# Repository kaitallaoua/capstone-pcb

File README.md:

# Analog Circuit Reliability for Low Earth Orbit Space Applications

In collaboration with the University of Saskatchewan, we are contributing a payload board
for the CubeSats Initiative in Canada for STEM (CUBICS). A CubeSat is a low cost, small
and approachable design for students “to engage in an end-to-end space mission
adapted to their needs and their level of comfort, expertise and readiness” (asc-csa.
gc.ca). Our payload studies the effects of space radiation on commonly used surface
mount analog Integrated Circuits (IC’s) in Low Earth Orbit (LEO). We compare different
shielding to see which provides a better effectiveness to weight ratio.

## Software

Available [here](https://github.com/kaitallaoua/capstone-cubeide)

## Setup

This project used KiCad `Version: 7.0.11-7.0.11~ubuntu22.04.1, release build` and a mix of windows builds.
Download KiCad [here](https://www.kicad.org/download/). KiCad 8 likely does work and I recommend you use it.

## Workflow

TBD (remove this once done): Someone needs to fork this repo to make further contributions to the project. Using an organization is best, I think UofS space team has one, maybe Regina team should make one? Regardless I will not be reviewing and accepting PR's to this repo.

Because using git for KiCad is like tracking binary files, I recommend to NOT rely on git handling merge conflicts. Avoid them entirely by letting only one person make changes on one branch at a time, make a PR, approve and merge and repeat and pass the baton to someone else to make changes.

## TODO

- Get I2C working (unlikely any KiCad changes)
- Get sinewave generation working 
- Add Voltage regulator
- Triple check we fit in PC104, on RADSAT-SK1 printout we dont fit in all holes, also supposed to be some notches?
- Optional: Use solder-attched external non volatile storage such as FLASH, EEPROM (or solder/glue micro sd down??)

The most substantial changes the sinwave generation. This task was assigned to Evan. Ultimately we could not get it working, thus I recommend to use a PWM wave gen from the mcu, likely add pre-amplification + current buffering, and pass it to a sharp drop off filter. The filter could be a dedicated one (probably better) or an op-amp driven one (butterworth?, wont have as good drop off without many stages).

UofRobotics is also making a PCB for their robot whose base is forked from this project, they may be a good reference for questions or idea sharing.

## Manufacturing

We used JLCPCB for `REV A` and `REV B` with great results. We also have nearly all parts ready for another revision. AT LEAST ONE MORE REVISION IS NEEDED SINCE THE FOLLOWING WERE FIXED AFTER `REV B`:

- IC1 footprint solder mask was incorrectly removed
- Micro SD card holder was facing the wrong way

Our manufacturing procedure was as follows:

Order from JLC (1 week delivery), Order from Mouser/Digikey (2-4 day delivery) -> Have all parts -> Go to ED435, use microscope, have one person assist finding parts, one pick+place, apply solder paste (min 4-5 hours)-> place in oven -> done

I recommend to use the parts list available from JLCPCB or PCBWay to assemble as much of the board for you as possible, it saves alot of time but honestly building it by hand it also not that bad. Either is fine.

## Resources

[KiCad 6 STM32 PCB Design Full Tutorial - Phil's Lab #65](https://www.youtube.com/watch?v=aVUqaB0IMh4)

[PCB Design Final Touches (Tips & Checklist) - Phil's Lab #131](https://www.youtube.com/watch?v=g4m91gv-4oQ)

## Front PCB

## Back PCB

## Front Copper Layer

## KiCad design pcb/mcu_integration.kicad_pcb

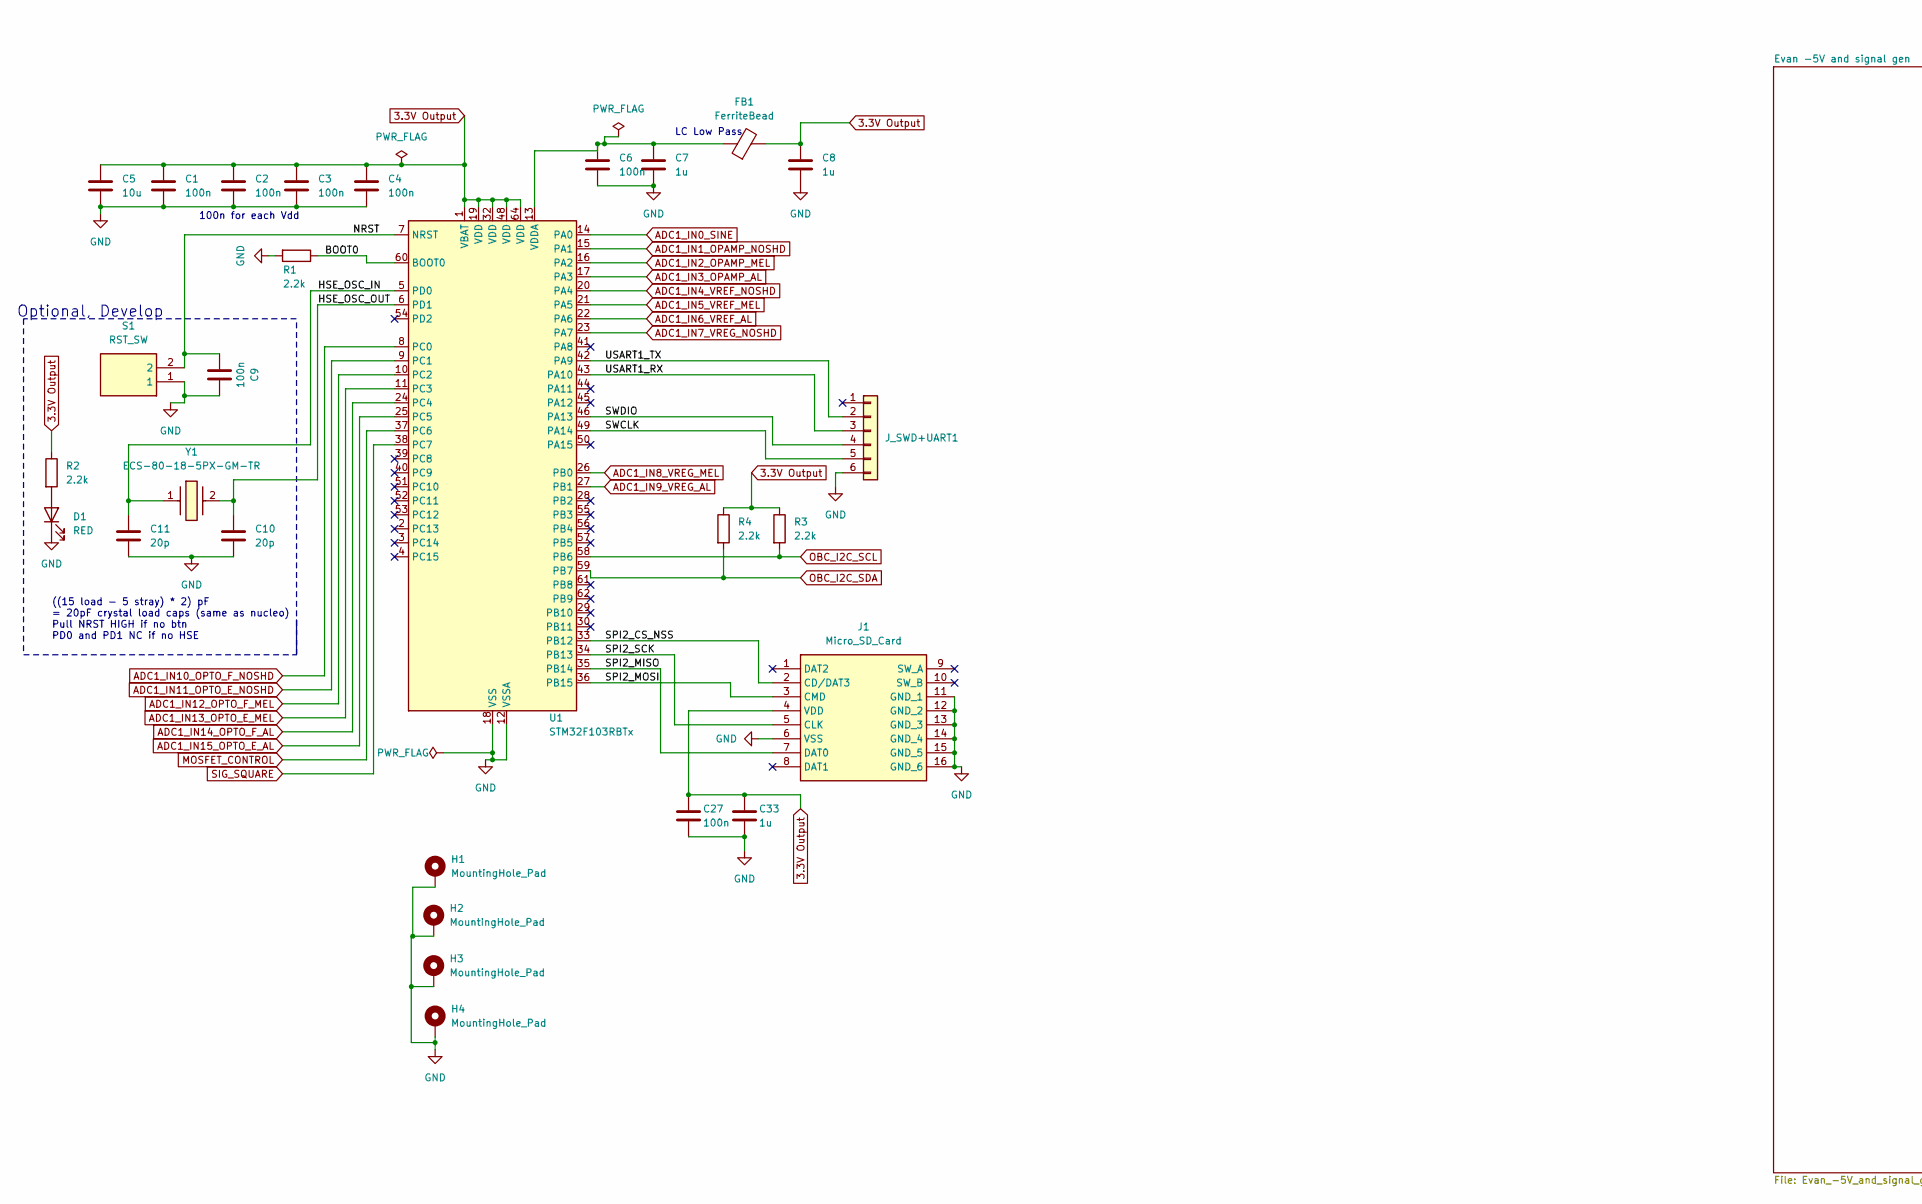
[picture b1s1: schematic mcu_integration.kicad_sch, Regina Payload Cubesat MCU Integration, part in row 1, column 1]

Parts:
C1: 100n; R_0402_1005Metric
C2, C3, C4, C6, C9, C27: 100n; C_0402_1005Metric
C5: 10u; C_0603_1608Metric
C7, C8, C33: 1u; C_0402_1005Metric
C10, C11: 20p; C_0402_1005Metric
D1: RED; LED_0603_1608Metric
FB1: FerriteBead; L_0603_1608Metric
H1, H2, H3, H4: MountingHole_Pad; MountingHole_3.2mm_M3_Pad_Via
J1: Micro_SD_Card; 22017781; Mouser Part Number 571-2201778-1
J_SWD+UART1: Conn_01x06; PinHeader_1x06_P2.54mm_Vertical
R1, R2, R3, R4: 2.2k; R_0402_1005Metric
S1: RST_SW; 95C04A3GWRT; Mouser Part Number 706-95C04A3GWRT
U1: STM32F103RBTx; LQFP-64_10x10mm_P0.5mm
Y1: ECS-80-18-5PX-GM-TR; ECS80185PXGMTR; Mouser Part Number 520-80-18-5PX-GM-TR

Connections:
3.3V Output: C1.1, C2.1, C3.1, C4.1, C5.1, C8.1, C27.1, C33.1, FB1.2, J1.4 (VDD), R2.1, R3.1, R4.1, U1.1 (VBAT), U1.19 (VDD), U1.32 (VDD), U1.48 (VDD), U1.64 (VDD); also elsewhere on the board
/BOOT0: R1.1, U1.60 (BOOT0)
/HSE_OSC_IN: C11.1, U1.5 (PD0), Y1.1
/HSE_OSC_OUT: C10.1, U1.6 (PD1), Y1.2
/NRST: C9.2, S1.2, U1.7 (NRST)
/SPI2_CS_NSS: J1.2 (CD/DAT3), U1.33 (PB12)
/SPI2_MISO: J1.7 (DAT0), U1.35 (PB14)
/SPI2_MOSI: J1.3 (CMD), U1.36 (PB15)
/SPI2_SCK: J1.5 (CLK), U1.34 (PB13)
/SWCLK: J_SWD+UART1.5, U1.49 (PA14)
/SWDIO: J_SWD+UART1.4, U1.46 (PA13)
/USART1_RX: J_SWD+UART1.3, U1.43 (PA10)
/USART1_TX: J_SWD+UART1.2, U1.42 (PA9)
ADC1_IN0_SINE: U1.14 (PA0); also elsewhere on the board
ADC1_IN1_OPAMP_NOSHD: U1.15 (PA1); also elsewhere on the board
ADC1_IN2_OPAMP_MEL: U1.16 (PA2); also elsewhere on the board
ADC1_IN3_OPAMP_AL: U1.17 (PA3); also elsewhere on the board
ADC1_IN4_VREF_NOSHD: U1.20 (PA4); also elsewhere on the board
ADC1_IN5_VREF_MEL: U1.21 (PA5); also elsewhere on the board
ADC1_IN6_VREF_AL: U1.22 (PA6); also elsewhere on the board
ADC1_IN7_VREG_NOSHD: U1.23 (PA7)
ADC1_IN8_VREG_MEL: U1.26 (PB0)
ADC1_IN9_VREG_AL: U1.27 (PB1)
ADC1_IN10_OPTO_F_NOSHD: U1.8 (PC0); also elsewhere on the board
ADC1_IN11_OPTO_E_NOSHD: U1.9 (PC1); also elsewhere on the board
ADC1_IN12_OPTO_F_MEL: U1.10 (PC2); also elsewhere on the board
ADC1_IN13_OPTO_E_MEL: U1.11 (PC3); also elsewhere on the board
ADC1_IN14_OPTO_F_AL: U1.24 (PC4); also elsewhere on the board
ADC1_IN15_OPTO_E_AL: U1.25 (PC5); also elsewhere on the board
GND: C1.2, C2.2, C3.2, C4.2, C5.2, C6.2, C7.2, C8.2, C9.1, C10.2, C11.2, C27.2, C33.2, D1.1 (K), H1.1, H2.1, H3.1, H4.1, J1.6 (VSS), J1.11 (GND_1), J1.12 (GND_2), J1.13 (GND_3), J1.14 (GND_4), J1.15 (GND_5), J1.16 (GND_6), J_SWD+UART1.6, R1.2, S1.1, U1.12 (VSSA), U1.18 (VSS), U1.31 (VSS), U1.47 (VSS), U1.63 (VSS); also elsewhere on the board
MOSFET_CONTROL: U1.37 (PC6); also elsewhere on the board
unnamed: D1.2 (A), R2.2
unnamed: C6.1, C7.1, FB1.1, U1.13 (VDDA)
OBC_I2C_SCL: R3.2, U1.58 (PB6); also elsewhere on the board
OBC_I2C_SDA: R4.2, U1.59 (PB7); also elsewhere on the board
SIG_SQUARE: U1.38 (PC7); also elsewhere on the board

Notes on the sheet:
((15 load - 5 stray) * 2) pF = 20pF crystal load caps (same as nucleo) Pull NRST HIGH if no btn PD0 and PD1 NC if no HSE
Optional, Develop
100n for each Vdd
LC Low Pass

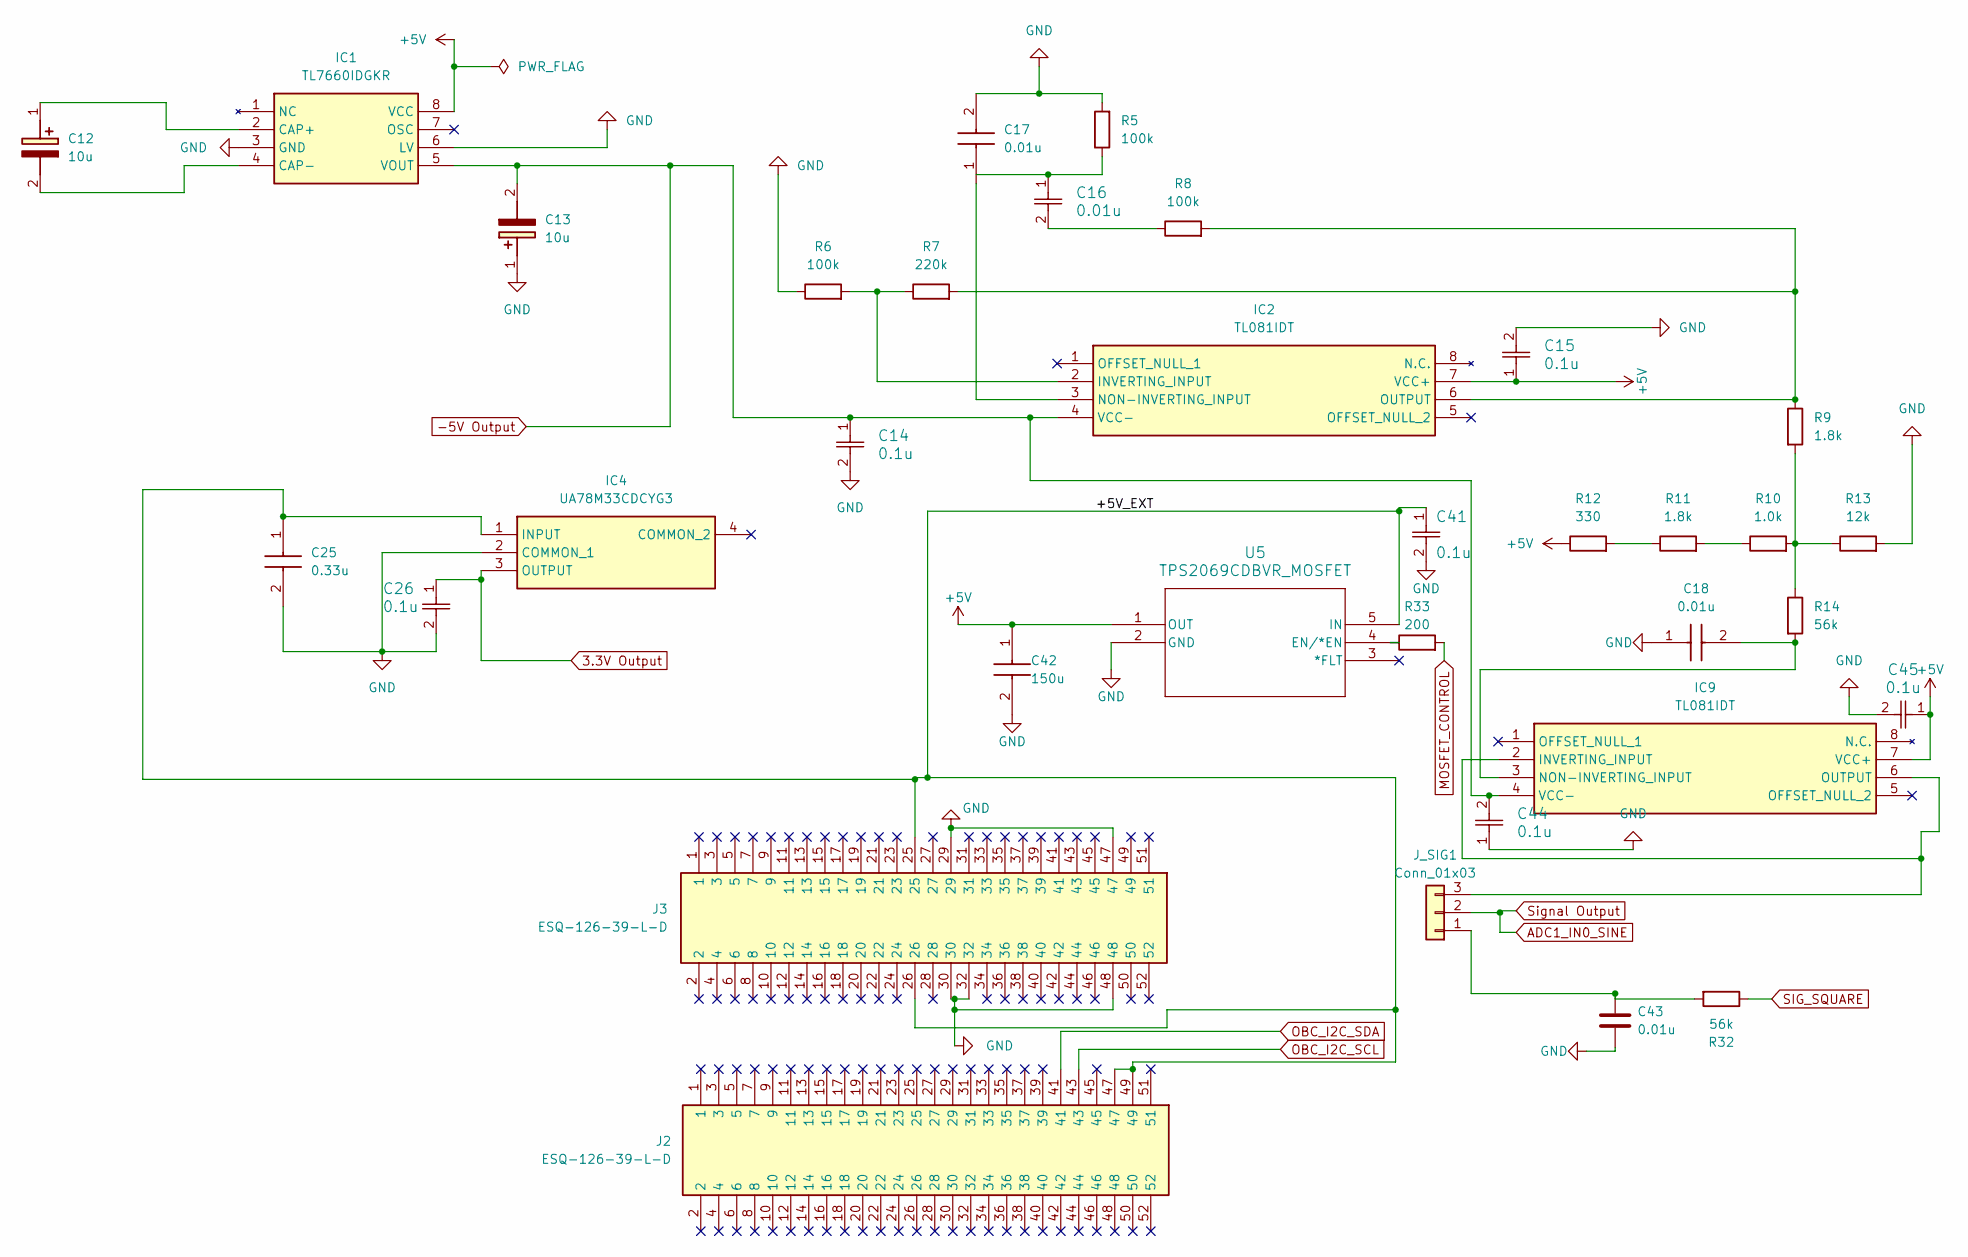
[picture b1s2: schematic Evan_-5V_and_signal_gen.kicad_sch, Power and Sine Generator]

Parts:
C12, C13: 10u; T495D; Mouser Part Number 80-T495D106K035
C14, C15, C26, C41, C44, C45: 0.1u; CAPC220145_88N_KEM-0.1u
C16: 0.01u; CAPC220145_88N_KEM-0.1u
C17, C18: 0.01u; C0805; Mouser Part Number 80-C0805C103F5G
C25: 0.33u; C0805; Mouser Part Number 80-C0805C334K3RAULR
C42: 150u; CAPC3225X280N_150U; Mouser Part Number 187-CL32A157MQVNNNE
C43: 0.01u; C0805
IC1: TL7660IDGKR; SOP65P490X110-8N-actual; Mouser Part Number 595-TL7660IDGKR
IC2, IC9: TL081IDT; SOIC127P600X175-8N; Mouser Part Number 511-TL081IDT
IC4: UA78M33CDCYG3; SOT230P700X180-4N; Mouser Part Number 595-UA78M33CDCYG3
J2, J3: ESQ-126-39-L-D; ESQ-126-Y-X-D; Mouser Part Number 200-ESQ12639LD
J_SIG1: Conn_01x03; PinHeader_1x03_P2.54mm_Vertical
R5, R6, R8: 100k; R_0402_1005Metric
R7: 220k; R_0402_1005Metric
R9, R11: 1.8k; R_0402_1005Metric
R10: 1.0k; R_0402_1005Metric
R12: 330; R_0402_1005Metric
R13: 12k; R_0402_1005Metric
R14, R32: 56k; R_0402_1005Metric
R33: 200; R_0402_1005Metric
U5: TPS2069CDBVR_MOSFET; DBV5_TEX_MF

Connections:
3.3V Output: C26.1, IC4.3 (OUTPUT); also elsewhere on the board
+5V: C15.1, C42.1, C45.1, IC1.8 (VCC), IC2.7 (VCC+), IC9.7 (VCC+), R12.1, U5.1 (OUT); also elsewhere on the board
-5V Output: C13.2 (-), C14.1, C44.2, IC1.5 (VOUT), IC2.4 (VCC-), IC9.4 (VCC-); also elsewhere on the board
/Evan -5V and signal gen/+5V_EXT: C25.1, C41.1, IC4.1 (INPUT), J2.47, J2.49, J3.25, J3.26, U5.5 (IN)
ADC1_IN0_SINE: J_SIG1.2; also elsewhere on the board
GND: C13.1 (+), C14.2, C15.2, C17.2, C18.1, C25.2, C26.2, C41.2, C42.2, C43.1, C44.1, C45.2, IC1.3 (GND), IC1.6 (LV), IC4.2 (COMMON_1), J3.29, J3.30, J3.32, J3.47, J3.48, R5.2, R6.1, R13.2, U5.2 (GND); also elsewhere on the board
MOSFET_CONTROL: R33.2; also elsewhere on the board
unnamed: C12.1 (+), IC1.2 (CAP+)
unnamed: C12.2 (-), IC1.4 (CAP-)
unnamed: C16.1, R5.1
unnamed: C16.2, R8.1
unnamed: IC2.2 (INVERTING_INPUT), R6.2, R7.1
unnamed: C17.1, IC2.3 (NON-INVERTING_INPUT)
unnamed: IC2.6 (OUTPUT), R7.2, R8.2, R9.1
unnamed: IC9.2 (INVERTING_INPUT), IC9.6 (OUTPUT), J_SIG1.3
unnamed: C18.2, IC9.3 (NON-INVERTING_INPUT), R14.2
unnamed: C43.2, J_SIG1.1, R32.2
unnamed: R10.1, R11.2
unnamed: R9.2, R10.2, R13.1, R14.1
unnamed: R11.1, R12.2
unnamed: R33.1, U5.4 (EN/*EN)
OBC_I2C_SCL: J2.43; also elsewhere on the board
OBC_I2C_SDA: J2.41; also elsewhere on the board
SIG_SQUARE: R32.1; also elsewhere on the board

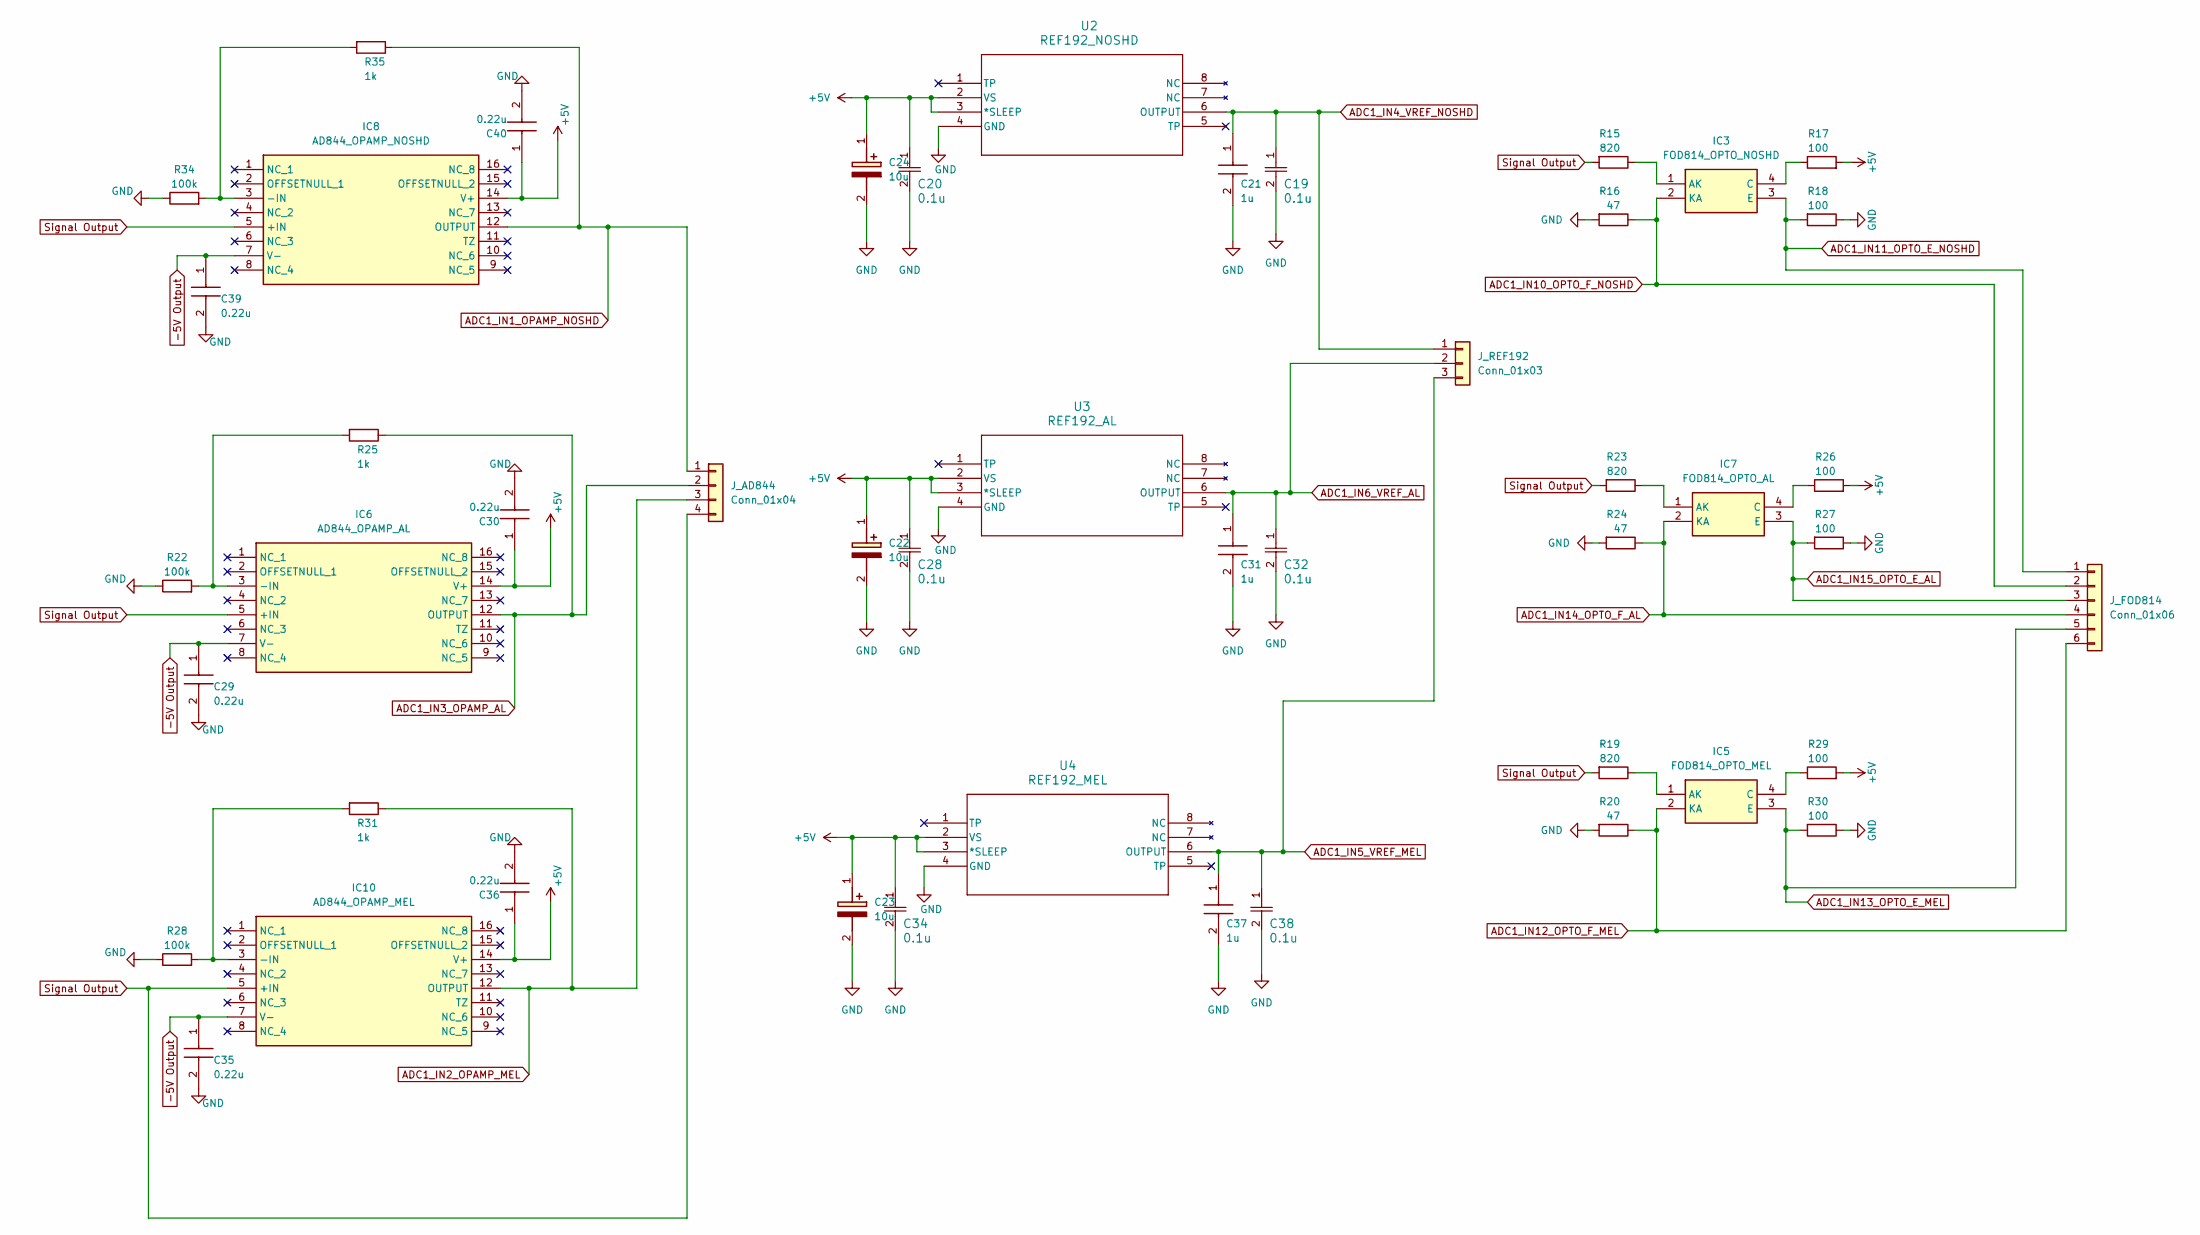
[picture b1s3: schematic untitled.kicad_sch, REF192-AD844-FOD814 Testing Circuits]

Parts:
C19, C20, C28, C32, C34, C38: 0.1u; CAPC220145_88N_KEM-0.1u
C21, C31, C37: 1u; C0805-1u; Mouser Part Number 80-C0805C105Z5VACTU
C22, C23, C24: 10u; T495D; Mouser Part Number 80-T495D106K035
C29, C30, C35, C36, C39, C40: 0.22u; C0805-0.22u; Manufacturer_Part_Number C0805C224M5VACTU
IC3: FOD814_OPTO_NOSHD; SOP254P1016X385-4N-FOD; Mouser Part Number 512-FOD814SD
IC5: FOD814_OPTO_MEL; SOP254P1016X385-4N-FOD; Mouser Part Number 512-FOD814SD
IC6: AD844_OPAMP_AL; SOIC127P1032X265-16N-AD844; Mouser Part Number 584-AD844JRZ-16-R7
IC7: FOD814_OPTO_AL; SOP254P1016X385-4N-FOD; Mouser Part Number 512-FOD814SD
IC8: AD844_OPAMP_NOSHD; SOIC127P1032X265-16N-AD844; Mouser Part Number 584-AD844JRZ-16-R7
IC10: AD844_OPAMP_MEL; SOIC127P1032X265-16N-AD844; Mouser Part Number 584-AD844JRZ-16-R7
J_AD844: Conn_01x04; PinHeader_1x04_P2.54mm_Vertical
J_FOD814: Conn_01x06; PinHeader_1x06_P2.54mm_Vertical
J_REF192: Conn_01x03; PinHeader_1x03_P2.54mm_Vertical
R15, R19, R23: 820; R_0402_1005Metric
R16, R20, R24: 47; R_0402_1005Metric
R17, R18, R26, R27, R29, R30: 100; R_0402_1005Metric
R22, R28, R34: 100k; R_0402_1005Metric
R25, R31, R35: 1k; R_0402_1005Metric
U2: REF192_NOSHD; R_8_ADI-REF
U3: REF192_AL; R_8_ADI-REF
U4: REF192_MEL; R_8_ADI-REF

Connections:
+5V: C20.1, C22.1 (+), C23.1 (+), C24.1 (+), C28.1, C30.1, C34.1, C36.1, C40.1, IC6.14 (V+), IC8.14 (V+), IC10.14 (V+), R17.2, R26.2, R29.2, U2.2 (VS), U2.3 (*SLEEP), U3.2 (VS), U3.3 (*SLEEP), U4.2 (VS), U4.3 (*SLEEP); also elsewhere on the board
-5V Output: C29.1, C35.1, C39.1, IC6.7 (V-), IC8.7 (V-), IC10.7 (V-); also elsewhere on the board
ADC1_IN0_SINE: IC6.5 (+IN), IC8.5 (+IN), IC10.5 (+IN), J_AD844.4, R15.2, R19.2, R23.2; also elsewhere on the board
ADC1_IN1_OPAMP_NOSHD: IC8.12 (OUTPUT), J_AD844.1, R35.1; also elsewhere on the board
ADC1_IN2_OPAMP_MEL: IC10.12 (OUTPUT), J_AD844.3, R31.1; also elsewhere on the board
ADC1_IN3_OPAMP_AL: IC6.12 (OUTPUT), J_AD844.2, R25.1; also elsewhere on the board
ADC1_IN4_VREF_NOSHD: C19.1, C21.1, J_REF192.1, U2.6 (OUTPUT); also elsewhere on the board
ADC1_IN5_VREF_MEL: C37.1, C38.1, J_REF192.3, U4.6 (OUTPUT); also elsewhere on the board
ADC1_IN6_VREF_AL: C31.1, C32.1, J_REF192.2, U3.6 (OUTPUT); also elsewhere on the board
ADC1_IN10_OPTO_F_NOSHD: IC3.2 (KA), J_FOD814.2, R16.1; also elsewhere on the board
ADC1_IN11_OPTO_E_NOSHD: IC3.3 (E), J_FOD814.1, R18.2; also elsewhere on the board
ADC1_IN12_OPTO_F_MEL: IC5.2 (KA), J_FOD814.6, R20.1; also elsewhere on the board
ADC1_IN13_OPTO_E_MEL: IC5.3 (E), J_FOD814.5, R30.2; also elsewhere on the board
ADC1_IN14_OPTO_F_AL: IC7.2 (KA), J_FOD814.4, R24.1; also elsewhere on the board
ADC1_IN15_OPTO_E_AL: IC7.3 (E), J_FOD814.3, R27.2; also elsewhere on the board
GND: C19.2, C20.2, C21.2, C22.2 (-), C23.2 (-), C24.2 (-), C28.2, C29.2, C30.2, C31.2, C32.2, C34.2, C35.2, C36.2, C37.2, C38.2, C39.2, C40.2, R16.2, R18.1, R20.2, R22.1, R24.2, R27.1, R28.1, R30.1, R34.1, U2.4 (GND), U3.4 (GND), U4.4 (GND); also elsewhere on the board
unnamed: IC3.1 (AK), R15.1
unnamed: IC3.4 (C), R17.1
unnamed: IC5.1 (AK), R19.1
unnamed: IC5.4 (C), R29.1
unnamed: IC6.3 (-IN), R22.2, R25.2
unnamed: IC7.1 (AK), R23.1
unnamed: IC7.4 (C), R26.1
unnamed: IC8.3 (-IN), R34.2, R35.2
unnamed: IC10.3 (-IN), R28.2, R31.2

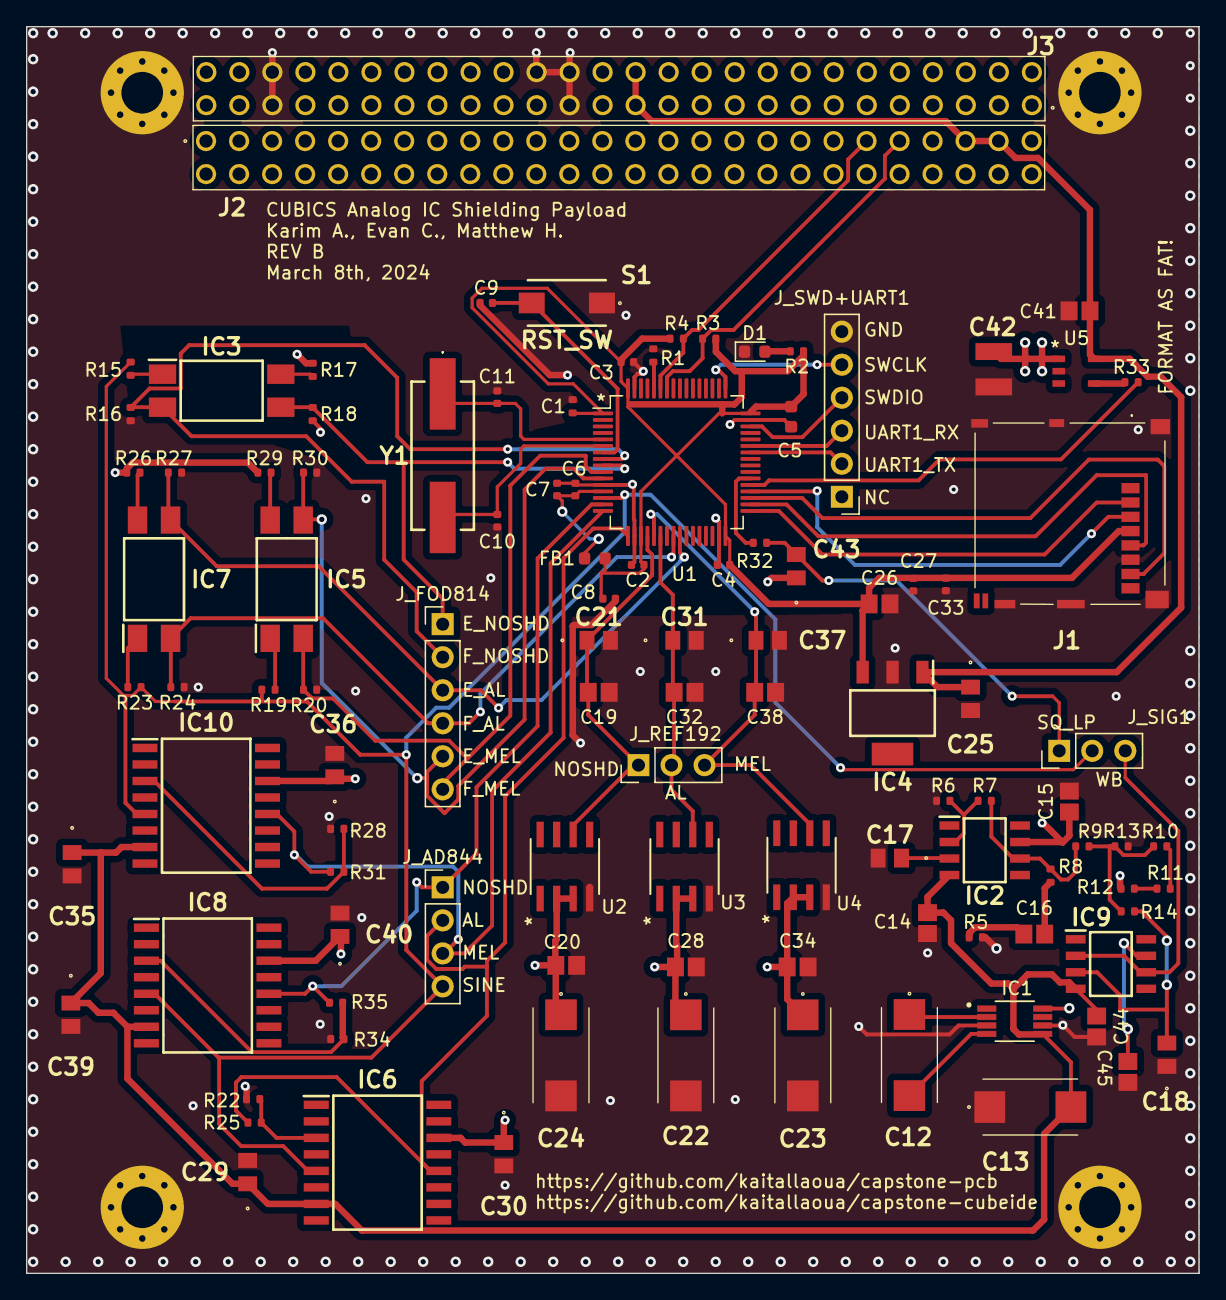
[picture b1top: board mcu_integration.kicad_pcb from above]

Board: 4 copper layers, 90.2 x 95.9 mm, 110 parts (0 on the bottom side), 59 nets.

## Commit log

2024-01-31 mcu_integration sch done
2024-02-06 mcu integration done, 10x10cm pcb+micro sd+osc
2024-02-06 Testing to see what works
2024-02-06 use generic dir
2024-02-06 use generic dir (#2)
2024-02-09 Signal gen and - 5 V circuits added
    I added the two circuits for signal gen and - 5 V all capacitators are speced and in the #links in discord.
2024-02-09 Signal gen and - 5 V circuits added (#3)
    I added the two circuits for signal gen and - 5 V all capacitators are speced and in the #links in discord.
2024-02-09 Changing of resistance values to make the signal voltage 3.0 V
    Changed resistors to make a better signal voltage
2024-02-13 Implemented IC Test portion (AD844, FOD814, REF192)
2024-02-13 Implemented IC Test portion (AD844, FOD814, REF192) (#5)
2024-02-14 Updated resistor values
    updated two resistor values to coincide with changes made to my circuit. R12 and R21 are the names.
2024-02-14 Added labels for ADC's, change R's and C's values to have more of same parts
2024-02-14 Added labels for ADC's, change R's and C's values to have more of same parts (#7)
2024-02-14 Evan---Adding_PC104_Connector
    Added the PC104 connector, added global -5v and signal output labels, changed r12 to 330, and added r21 of 150k.
2024-02-14 Evan---Adding_PC104_Connector (#8)
    Added the PC104 connector, added global -5v and signal output labels, changed r12 to 330, and added r21 of 150k.
2024-02-15 Adding 3.3v reg
    added 3.3v regulator circuit.
2024-02-15 Adding 3.3v reg (#9)
    added 3.3v regulator circuit.
2024-02-16 first bulk commit of routing
2024-02-18 removed about 300 warnings
2024-02-18 removed all pcb DRC errors/warnings
2024-02-18 silkscreen: remove part num from inside part, cleanup
2024-02-18 add silk labels for each pin, my final cleanup
2024-02-18 remove all errors and suppress unspecified connections warnings in schematic ERC
2024-02-18 First Major PCB layout and routing (#10)
    * first bulk commit of routing
    * removed about 300 pcb ERC warnings
    * removed all pcb DRC errors/warnings
    * silkscreen: remove part num from inside part, cleanup
    * add silk labels for each pin, my final cleanup
    * remove all errors and suppress unspecified connections warnings in schematic ERC
2024-02-20 Implemented mosfet, decoupling
    Please review functionality
2024-02-20 wire placement, inital revisions
    made it more PCB ready with spacing and such
2024-02-20 Wire touchup, initial changes (#12)
    * Implemented mosfet, decoupling
    Please review functionality
    * wire placement, inital revisions
    made it more PCB ready with spacing and such
2024-02-20 MOSFET connections updated
    updated the MOSFET connection to control the 5V plane and added a separate line going directly to the 3.3V regulator.
2024-02-20 rotate U5 silk
2024-02-20 MOSFET connections updated (#13)
    * MOSFET connections updated
    updated the MOSFET connection to control the 5V plane and added a separate line going directly to the 3.3V regulator.
    * rotate U5 silk
    ---------
2024-02-21 Updated vias from micro to through hole
    Please check to ensure there are no more micro vias.
2024-02-22 (accepted by jlc) Updated vias from micro to through hole (#14)
    Please check to ensure there are no more micro vias.
2024-02-27 update README with images, add BOM, schematic pdf, update evan sch title
2024-02-27 update README with images, add BOM, schematic pdf, update evan sch title (#15)
2024-02-29 done layout/ratsnet
2024-03-02 95% of second rev done, just two errors
2024-03-03 Karim start 2nd rev (#16)
    * done layout/ratsnet
    * 95% of second rev done, just two errors
2024-03-06 fix +5v connection, make final via
2024-03-06 connect mcu 3.3vreg to +5v_ext so it always has power
2024-03-06 fix +5v connection, make final via (#17)
    * fix +5v connection, make final via
    * connect mcu 3.3vreg to +5v_ext so it always has power
2024-03-06 fixed all errors and warnings, silk fixed
2024-03-06 add names to project
2024-03-08 misc cleanup
2024-03-08 TL766 footprint fixed
2024-03-08 proper holes added
2024-03-08 hole sizing done, evan cap fix
2024-03-09 mcu square wave sine header, more space for ic's should be ready for order
2024-03-09 ready for jlcpcb
2024-03-09 cleanup README
2024-03-09 close kicad before commit
2024-03-11 (accepted by jlc rev B) Karim rev2 cleanup (#18)
    * fixed all errors and warnings, silk fixed
    * add names to project
    * misc cleanup
    * TL766 footprint fixed
    * proper holes added
    * hole sizing done, evan cap fix
2024-03-12 soldermask applied to ic1
2024-03-12 soldermask applied to ic1 (#19)
2024-03-13 rotate sd 180 since was wrong, cleanup, add gnd vias on edge
2024-03-13 rotate sd 180 since was wrong, cleanup, add gnd vias on edge (#20)
2024-03-16 Added-Voltage-follower-and-Changed-opto-resistor-values
    Added the voltage follower circuit to the signal gen. Changed the R values on the optoisolator circuit.
2024-03-17 Added-Voltage-follower-and-Changed-opto-resistor-values (#21)
    Added the voltage follower circuit to the signal gen. Changed the R values on the optoisolator circuit.
2024-03-23 clean evan schematic
2024-03-23 update schematic pdf
2024-03-23 clean evan schematic (#22)
    * clean evan schematic
    * update schematic pdf
2024-04-08 update README and add project day docs
2024-04-08 add reference to software repo
2024-04-09 add links to usefel yt videos
